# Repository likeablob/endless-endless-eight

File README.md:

<p align="center">
  
  <p align="center">
  <small>The clip played is from The Melancholy of Haruhi Suzumiya (2009). </small>
  </p>
</p>

# Endless Endless Eight

A self-sustained AVI player to replay the summer days.

- ESP32 to play MJPEG-AVI video files from microSD at 24 fps.
- Utilizes ULP coprocessor for BAT voltage monitoring, Deep Sleep management etc.
- 5V solar panel and small LiPo battery as the main power source.
- (Planned) LTC3130-1 for more efficient power conversion.

## BOM

**WIP**

- ESP32 WeMos LOLIN32 Lite
- ST7735 80x160 LCD module
- microSD card (>= 2 GB)
- 5V 2W solar panel

## Prepare video files

All the video files to be placed on the MicroSD must be MJPEG-encoded AVI.

```sh
# Transcode EP 12~19 to ee_%d.avi, with scaling and cropping
$ seq 12 19 | xargs -L 1 -P1 -I% bash -c 'ffmpeg -i ee_%.mp4 -r 24 -vf scale=160:-1,crop=160:80 -vcodec mjpeg -q:v 5 -an ee_%.avi -y'
```

See [sdcard/](./sdcard/) for a set of sample vid files. These are converted from [BigBuckBunny.mp4](http://commondatastorage.googleapis.com/gtv-videos-bucket/sample/BigBuckBunny.mp4).

```sh
# The sample vid files were from
$ seq 12 19 | xargs -L 1 -P1 -I% bash -c 'ffmpeg -ss $(((% - 12)*2)) -to $(((% - 12 + 1) * 2)) -i BigBuckBunny.mp4 -r 24 -vf scale=160:-1,crop=160:80 -vcodec mjpeg -q:v 5 -an ee_%.avi -y'
```

## Build firmware

```sh
$ git clone https://github.com/likeablob/endless-endless-eight.git
$ cd endless-endless-eight

$ cp include/user_config.g.template cp include/user_config.h
$ code include/user_config.h

$ pio run || pio run # The very 1st run may fail due to ulptool-pio
$ pio run -t upload
```

## Print enclosure

See [./enclosure](./enclosure).

## How it works

### State transitions

Centering on the deep sleep mode, this application has several wake-up states as depicted in the following diagram.

- The application switches back-and-forth between the nominal mode and deep sleep depending on the battery voltage. (See [Power management strategy](#power-management-strategy) for details.)
- Also, under the certain condition, it wakes in;
  - Emergency mode to prepare for a complete power loss (See [State persistence](#state-persistence))
  - Periodic Reporting mode for reporting housekeeping data via MQTT
- Basically every wake up transition is triggered by the ULP routine.

```mermaid
stateDiagram-v2
    Playing: Playing Video (Nominal)
    [*] --> Playing
    Playing --> DeepSleep: At low battery
    DeepSleep --> Playing: At high battery

    DeepSleep --> Emergency: At very low battery
    Emergency --> DeepSleep: ASAP

    DeepSleep --> PeriodicReporting: Every 30 minutes
    PeriodicReporting --> DeepSleep: ASAP
```

### Power management strategy

It's quite simple; Wake the Main CPU up if `the battery voltage (BAT_V) >= 3.9 V` and put into sleep if `BAT_V <= 3.75 V`.  
The ULP co-processor executes own routine every one second, but still is able to keep the deep sleep current consumption at uA-level.

```mermaid
flowchart TB
  subgraph CPU["Main CPU"]
    %% flow
    power_boot(" ")
    boot("Boot")
    check_ulp_boot{"Wake by ULP?"}
    init_ulp["Init ULP routine"]

    %% flow
    init_loop(" ")
    check_batv_sleep{"BAT_V <= SLEEP_TH"}
    sleep("Deep sleep")

    power_boot --> boot --> check_ulp_boot
    check_ulp_boot -->|"Yes"| init_loop
    check_ulp_boot -->|"No"| init_ulp --> init_loop

    init_loop --> check_batv_sleep
    check_batv_sleep -->|"Yes"| sleep
    check_batv_sleep -->|"No"| init_loop
    sleep -.-> |"Wake by ULP"| boot
  end

  subgraph ULP
    %% nodes
    boot_ulp(" ")
    measure_batv["Measure Battery voltage (BAT_V) by ADC"]
    check_batv_wake{"BAT_V >= WAKE_TH"}
    wake_main["Wake Main CPU"]
    end_ulp(" ")

    %% flow
    boot_ulp --> measure_batv --> check_batv_wake
    check_batv_wake -->|"Yes"| wake_main ---> end_ulp
    check_batv_wake --->|"No"| end_ulp

    end_ulp -.->|"Every 1 sec"| boot_ulp
  end

  %% flow
  init_ulp -.-> boot_ulp
```

### State persistence

The play state such as a file playing, its position and loop count etc. are kept over deep sleep or even complete power outage, thanks to ~~Nagato~~ [RTC SLOW MEM](https://docs.espressif.com/projects/esp-idf/en/latest/esp32/api-reference/system/sleep_modes.html#overview) and [Non-Volatile Storage](https://docs.espressif.com/projects/esp-idf/en/latest/esp32/api-reference/storage/nvs_flash.html). The former is volatile but survives deep sleep, and the latter is nothing but a reserved region in flash.

In short there are two pathways for each storage.

- A. Save to `RTC_SLOW_MEM` before entering deep sleep. Restore from `RTC_SLOW_MEM` after waking up from deep sleep.
- B. Save to `NVS` at very-low battery voltage. Restore from `NVS` on boot.

Note: About B., the ULP routine wakes the main CPU in the Emergency mode when `BAT_V <= 3.55 V`. This happens only once and the related flag will be cleared by the main CPU after normal wake up.

```mermaid
flowchart
  %% nodes
  init(" ")
  check_ulp_boot{"Wake by ULP?"}
  restore_from_nvs["Restore from Non-volatile storage"]
  restore_from_rtc["Restore from RTC SLOW RAM\n(Volatile, Deep-sleep persistent)"]
  check_ulp_flag_emergency{"Emergency Mode?\n(caused by very low battery)"}
  save_to_nvs["Save to Non-volatile storage"]
  sleep("Deep sleep")
  init_loop("Main Loop")
  check_low_bat{"Low battery?"}
  save_to_rtc["Save to RTC SLOW MEM"]

  init ---> check_ulp_boot
  check_ulp_boot -->|"Yes"| check_ulp_flag_emergency
  check_ulp_boot -->|"No"| restore_from_nvs --> init_loop
  check_ulp_flag_emergency --> |"Yes"| save_to_nvs --> sleep
  check_ulp_flag_emergency --> |"No"| restore_from_rtc --> init_loop

  init_loop --> check_low_bat
  check_low_bat --> |"Yes"| save_to_rtc --> sleep
  check_low_bat --> |"No"| init_loop

  sleep -.-> init

  classDef restore fill:#dce4ef,stroke:#333,stroke-width:2px;
  classDef save fill:#e7f4e4,stroke:#333,stroke-width:2px;
  class restore_from_nvs,restore_from_rtc restore
  class save_to_nvs,save_to_rtc save
```

## LICENSE

MIT

## Dependencies

This projects is here thanks to a lot of superb OSS libraries.
See [platformio.ini](./platformio.ini) for details. Thank you to all the devs.

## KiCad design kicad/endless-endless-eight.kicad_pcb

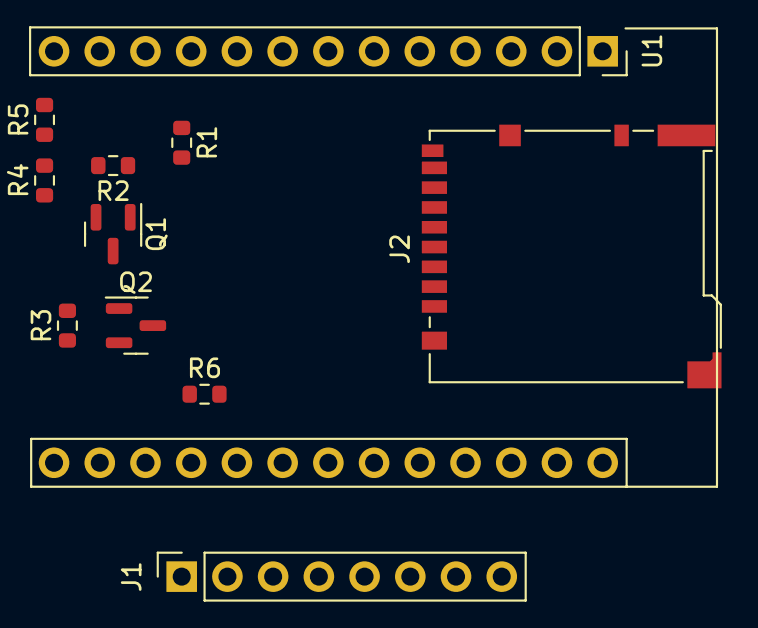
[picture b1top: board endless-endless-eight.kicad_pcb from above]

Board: 2 copper layers, 11 parts (0 on the bottom side), 18 nets, no tracks yet.

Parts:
J1: 0.96in_80x160_st7735s_LCD_module; PinSocket_1x08_P2.54mm_Vertical
J2: Micro_SD_Card_Det; microSD_HC_Hirose_DM3BT-DSF-PEJS
Q1: Q_NMOS_GSD; SOT-23
Q2: Q_PMOS_GSD; SOT-23
R1: 100; R_0603_1608Metric
R2, R3, R4, R5: 10k; R_0603_1608Metric
R6: 2k; R_0603_1608Metric
U1: esp32_wemos_lolin32_lite

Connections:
+3V3: Q2.2 (S), R3.1, U1.26 (3v3)
BAT_V_MON: R4.2, R5.1, U1.4 (34)
BUS_POWER: J1.2, J2.4 (VDD), Q2.3 (D), R6.1
BUS_POWER_SW: R1.1, U1.9 (26)
LCD_CS: J1.7, U1.21 (5)
LCD_DC: J1.6, U1.20 (17)
LCD_GND: J1.1, J2.6 (VSS), Q1.2 (S), R2.2, R5.2, U1.13 (GND)
LCD_RES: J1.5, U1.19 (16)
LCD_SCL: J1.3, U1.22 (18)
LCD_SDA: J1.4, U1.23
unnamed: Q1.1 (G), R1.2, R2.1
unnamed: Q1.3 (D), Q2.1 (G), R3.2
SDIO_CLK: J2.5 (CLK), U1.11 (14)
SDIO_CMD: J2.3 (CMD), U1.15
SDIO_DAT0: J2.7 (DAT0), R6.2, U1.16 (2)
SDIO_DAT1: J2.8 (DAT1), U1.18 (4)
SDIO_DAT2: J2.1 (DAT2), U1.12
SDIO_DAT3: J2.2 (DAT3/CD), U1.14 (13)

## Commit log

2022-02-14 Add files
2022-02-14 Add sample vids
2022-02-16 Init mqtt_reporter correctly on pediodic wake
2022-02-19 Better ADC ref voltage based on measurements
2022-02-19 Turn off BUILTIN_LED by default
2022-02-19 Workaround for stable wake-up after WiFi.disconnect(true)
2022-02-19 Migrate backup variables to RTC_DATA_ATTR
2022-02-19 Implement emergency mode for saving variables into non-volatile memory
    - Add `loopCount` to EEE for tracking number of files played.
    - Implement emergency mode in main app:
    - Save variables (frameInd, etc.) to non-volatile memory when it's woken in
    the Emergency mode where BAT voltage is below the threshold.
    - Use Preferences Library (which is backed by ESP32 nvs) as storage backend.
    - Minor fix to let the main code to clear WAKE_VOLTAGE_SATISFIED flag just before
2022-02-19 Increase PM_VBAT_TH_EMERGENCY slightly
2022-02-19 Add how-it-works section
2022-02-23 Start deep sleep on error instead of reset
2022-02-23 Log batV on wake
2022-03-06 Add schematics made with EESchema
2022-03-06 Apply LPF to ULP ADC reading
2022-03-06 Add .scad and .stls of casing
2022-03-06 Change PIN_BUS_POWER_SW to 26
2022-03-06 Add enclosure/README
